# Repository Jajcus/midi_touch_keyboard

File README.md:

# MIDI Touch Keyboard

**Disclaimer**: this is a one-time personal hobby project. Shared as-is. Work
in progress. **Use at your own risk**, if at all.

This project is a device that lets you play MIDI synthesizer by touching
conducting surfaces, like fruits or vegetables.

It has 16 inputs (a bit over an octave), standard DIN-5 MIDI output and USB
MIDI interface. Additional controls include 'calibrate' button and a
'sensitivity' potentiometer.

A LED strip provides additional feedback displaying key state in piano-like layout.

## Working principle

Each 'input' is a simple capacitive sensor. Touching it either significantly
increases input capacitance or lowers its resistance to the device's ground. In
both cases this causes increase in the time constant of an RC circuit monitored
by a microcontroller.

The microcontroller charges the capacitance of the sensor circuit in short
intervals and checks if it discharges before a specific time. If it does, then
the input is open if it does not, it means the sensor has been touched.

The time to wait for discharging is determined through a calibration process
and the sensitivity potentiometer. The calibration process just measures the discharge times,
and collects maximum and minimum values measured, to roughly find the threshold
range. This assumes that at least one of the sensors has been touched during calibration.
Then the sensitivity knob can be used to set threshold within this range.

## Circuit design

The heart of the device is a Raspberry Pi Pico board. Cheap and powerful enough.

The sensor inputs are built using two resistors and a capacitor connected do
the microcontroller general-purpose IO pins. Values of those components has
been chosen experimentally to get quick and precise-enough measurements.

One pin is used to drive MIDI output. That is a standard circuit from the MIDI
1.0 specification using a transistor as the current loop switch (with a
Schottky diode for sharper edges).

Another pin drives addressable LED strip (WS2812B). Again, a transistor with a
Schottky diode is used to drive 5V data line here.

Two pins are used for button (actually only one used at the moment).

One ADC pin is connected to the sensitivity potentiometer. Another ADC pin is
connected to the sensors connector, so it can be used for detection of a device
connected there (in case I make one).

There is also an additional DC input, in case the micro-USB on the Pico is not
enough, because why not.

## Hardware realization

The device has been built on a single 'DIY' double-sided PCB, manufactured on a
small CNC engraver. Brass rivets are used for vias, otherwise no holes are
copper-plated. Most elements are surface mounted, 0603 size. The Raspberry Pi
Pico board is also surface-soldered to the main PCB, to keep overall low
profile (which the MIDI jack breaks anyway).

Sensor inputs are available via an angled 2x20 pin connector (like for an
old-style IDE HDD ribbon). Lower pins are all ground, sensors are on the upper
pins, starting from the third one. The last upper pin measures resistance to
the ground, for some auto-configuration capability in the future (not used now).

PCB layout is designed for my DIY constraints and the way I imagined the
complete device and is not suitable for most other fabrication processes.

The PCB design from KiCAD has been exported to Gerber files which would first
be converted to gcode by [pcb2gcode](https://github.com/pcb2gcode/pcb2gcode)
and then that gcode would be further processed by my
[postprocess.py](kicad/postprocess.py) script, for easier use with
[bCNC](https://github.com/vlachoudis/bCNC). Then couple of attempts and many
hours with the CNC machine and the PCB was ready for soldering. No soldermask,
unfortunately.

Even without the soldermask and with the small SMD components soldering was not
very hard. There was just a couple places that needed a do-over and proper
cleanup (the sensor circuit is quite sensitive to bad isolation, as 10 megaohm
resistors are used there).

The holes were drilled a bit to shallow, but that was not hard to fix, either.

## Firmware

The firmware is written in Rust, using the marvelous
[Embassy](https://embassy.dev/) framework. Nothing fancy otherwise.

One CPU core is dedicated for reading the sensors and UI inputs and basic
key-on/key-off logic. The other core does MIDI I/O over serial and USB.
Components communicate by passing messages via Embassy channels.

The LED strip programming uses Raspberry Pi Pico's PIO (programmable I/O), so
no bit-banging in CPU time is needed.

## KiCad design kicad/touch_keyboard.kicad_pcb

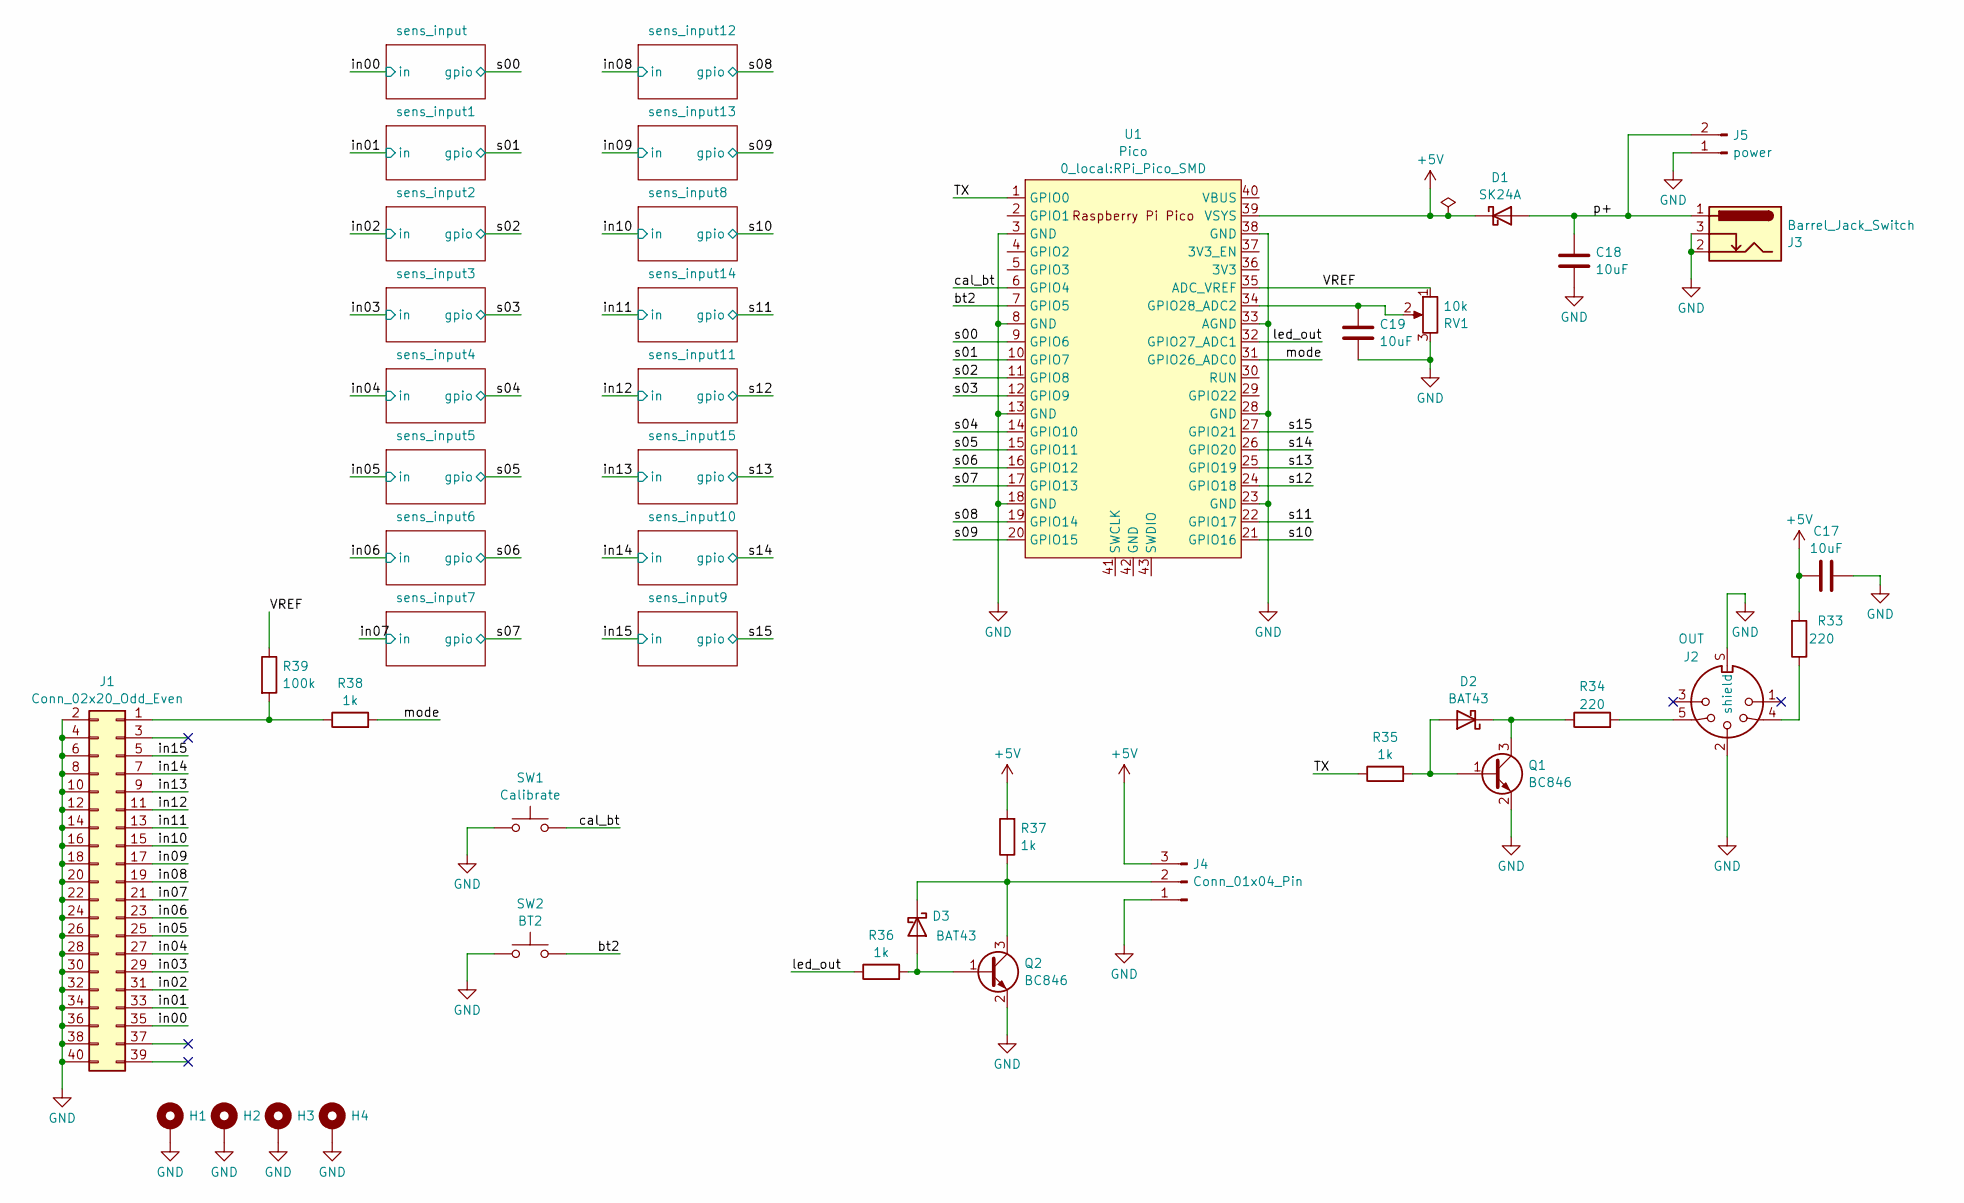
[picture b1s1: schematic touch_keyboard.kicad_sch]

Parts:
C17, C18, C19: 10uF; C_0805_2012Metric
D1: SK24A; D_SMA-SMB_Universal_Handsoldering
D2, D3: BAT43; D_MiniMELF
H1, H2, H3, H4: MountingHole_Pad; MountingHole_3.2mm_M3_DIN965_Pad
J1: Conn_02x20_Odd_Even; PinHeader_2x20_P2.54mm_Horizontal
J2: OUT; DIN_5
J3: Barrel_Jack_Switch; BarrelJack_CUI_PJ-063AH_Horizontal
J4: Conn_01x04_Pin; PinHeader_1x03_P2.54mm_Horizontal
J5: power; PinHeader_1x02_P2.54mm_Horizontal
Q1, Q2: BC846; SOT-23
R33, R34: 220; R_0603_1608Metric; MPN C22962
R35, R36, R37, R38: 1k; R_0603_1608Metric; MPN C22962
R39: 100k; R_0603_1608Metric; MPN C22962
RV1: 10k; Potentiometer_Bourns_PTV09A-1_Single_Vertical
SW1: Calibrate; Button
SW2: BT2; Button
U1: Pico; RPi_Pico_SMD

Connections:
+5V: C17.1, D1.1 (K), J4.3, R33.2, R37.2, U1.39 (VSYS)
/TX: R35.1, U1.1 (GPIO0)
/VREF: R39.1, RV1.1, U1.35 (ADC_VREF)
/bt2: SW2.2, U1.7 (GPIO5)
/cal_bt: SW1.2, U1.6 (GPIO4)
/in00: J1.35; also elsewhere on the board
/in01: J1.33; also elsewhere on the board
/in02: J1.31; also elsewhere on the board
/in03: J1.29; also elsewhere on the board
/in04: J1.27; also elsewhere on the board
/in05: J1.25; also elsewhere on the board
/in06: J1.23; also elsewhere on the board
/in07: J1.21; also elsewhere on the board
/in08: J1.19; also elsewhere on the board
/in09: J1.17; also elsewhere on the board
/in10: J1.15; also elsewhere on the board
/in11: J1.13; also elsewhere on the board
/in12: J1.11; also elsewhere on the board
/in13: J1.9; also elsewhere on the board
/in14: J1.7; also elsewhere on the board
/in15: J1.5; also elsewhere on the board
/led_out: R36.1, U1.32 (GPIO27_ADC1)
/mode: R38.2, U1.31 (GPIO26_ADC0)
/p+: C18.2, D1.2 (A), J3.1, J5.2
/s00: U1.9 (GPIO6); also elsewhere on the board
/s01: U1.10 (GPIO7); also elsewhere on the board
/s02: U1.11 (GPIO8); also elsewhere on the board
/s03: U1.12 (GPIO9); also elsewhere on the board
/s04: U1.14 (GPIO10); also elsewhere on the board
/s05: U1.15 (GPIO11); also elsewhere on the board
/s06: U1.16 (GPIO12); also elsewhere on the board
/s07: U1.17 (GPIO13); also elsewhere on the board
/s08: U1.19 (GPIO14); also elsewhere on the board
/s09: U1.20 (GPIO15); also elsewhere on the board
/s10: U1.21 (GPIO16); also elsewhere on the board
/s11: U1.22 (GPIO17); also elsewhere on the board
/s12: U1.24 (GPIO18); also elsewhere on the board
/s13: U1.25 (GPIO19); also elsewhere on the board
/s14: U1.26 (GPIO20); also elsewhere on the board
/s15: U1.27 (GPIO21); also elsewhere on the board
GND: C17.2, C18.1, C19.1, H1.1, H2.1, H3.1, H4.1, J1.2, J1.4, J1.6, J1.8, J1.10, J1.12, J1.14, J1.16, J1.18, J1.20, J1.22, J1.24, J1.26, J1.28, J1.30, J1.32, J1.34, J1.36, J1.38, J1.40, J2.2, J2.S (shield), J3.2, J3.3, J4.1, J5.1, Q1.2 (E), Q2.2 (E), RV1.3, SW1.1, SW2.1, U1.3 (GND), U1.8 (GND), U1.13 (GND), U1.18 (GND), U1.23 (GND), U1.28 (GND), U1.33 (AGND), U1.38 (GND); also elsewhere on the board
unnamed: D2.2 (A), Q1.1 (B), R35.2
unnamed: D2.1 (K), Q1.3 (C), R34.1
unnamed: D3.2 (A), Q2.1 (B), R36.2
unnamed: D3.1 (K), J4.2, Q2.3 (C), R37.1
unnamed: J1.1, R38.1, R39.2
unnamed: J2.4, R33.1
unnamed: J2.5, R34.2
unnamed: C19.2, RV1.2, U1.34 (GPIO28_ADC2)

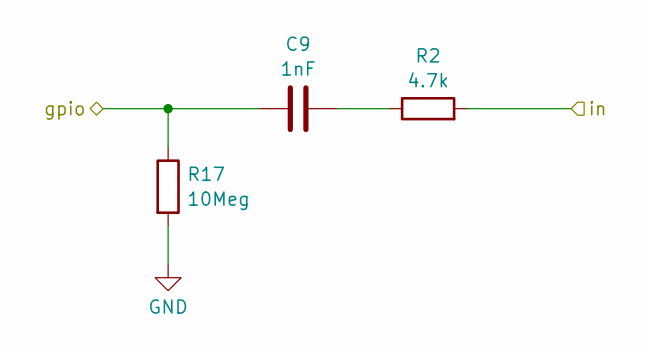
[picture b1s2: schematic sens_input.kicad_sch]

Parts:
C9: 1nF; C_0603_1608Metric
R2: 4.7k; R_0603_1608Metric
R17: 10Meg; R_0603_1608Metric

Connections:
/in00: R2.2; also elsewhere on the board
/s08: C9.1, R17.1; also elsewhere on the board
GND: R17.2; also elsewhere on the board

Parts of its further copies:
C1, C2, C3, C4, C5, C6, C7, C8, C10, C11, C12, C13, C14, C15, C16: 1nF; C_0603_1608Metric
R1, R3, R5, R7, R9, R11, R13, R15, R19, R21, R23, R25, R27, R29, R31: 10Meg; R_0603_1608Metric
R4, R6, R8, R10, R12, R14, R16, R18, R20, R22, R24, R26, R28, R30, R32: 4.7k; R_0603_1608Metric

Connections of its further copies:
/in01: R4.2; also elsewhere on the board
/in02: R6.2; also elsewhere on the board
/in03: R8.2; also elsewhere on the board
/in04: R10.2; also elsewhere on the board
/in05: R12.2; also elsewhere on the board
/in06: R14.2; also elsewhere on the board
/in07: R16.2; also elsewhere on the board
/in08: R18.2; also elsewhere on the board
/in09: R20.2; also elsewhere on the board
/in10: R22.2; also elsewhere on the board
/in11: R24.2; also elsewhere on the board
/in12: R26.2; also elsewhere on the board
/in13: R28.2; also elsewhere on the board
/in14: R30.2; also elsewhere on the board
/in15: R32.2; also elsewhere on the board
/s00: C1.1, R1.1; also elsewhere on the board
/s01: C2.1, R3.1; also elsewhere on the board
/s02: C3.1, R5.1; also elsewhere on the board
/s03: C4.1, R7.1; also elsewhere on the board
/s04: C5.1, R9.1; also elsewhere on the board
/s05: C6.1, R11.1; also elsewhere on the board
/s06: C7.1, R13.1; also elsewhere on the board
/s07: C8.1, R15.1; also elsewhere on the board
/s09: C10.1, R19.1; also elsewhere on the board
/s10: C11.1, R21.1; also elsewhere on the board
/s11: C12.1, R23.1; also elsewhere on the board
/s12: C13.1, R25.1; also elsewhere on the board
/s13: C14.1, R27.1; also elsewhere on the board
/s14: C15.1, R29.1; also elsewhere on the board
/s15: C16.1, R31.1; also elsewhere on the board
GND: R1.2, R3.2, R5.2, R7.2, R9.2, R11.2, R13.2, R15.2, R19.2, R21.2, R23.2, R25.2, R27.2, R29.2, R31.2; also elsewhere on the board
unnamed: C2.2, R4.1
unnamed: C3.2, R6.1
unnamed: C4.2, R8.1
unnamed: C5.2, R10.1
unnamed: C6.2, R12.1
unnamed: C7.2, R14.1
unnamed: C8.2, R16.1
unnamed: C10.2, R20.1
unnamed: C11.2, R22.1
unnamed: C12.2, R24.1
unnamed: C13.2, R26.1
unnamed: C14.2, R28.1
unnamed: C15.2, R30.1
unnamed: C16.2, R32.1

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
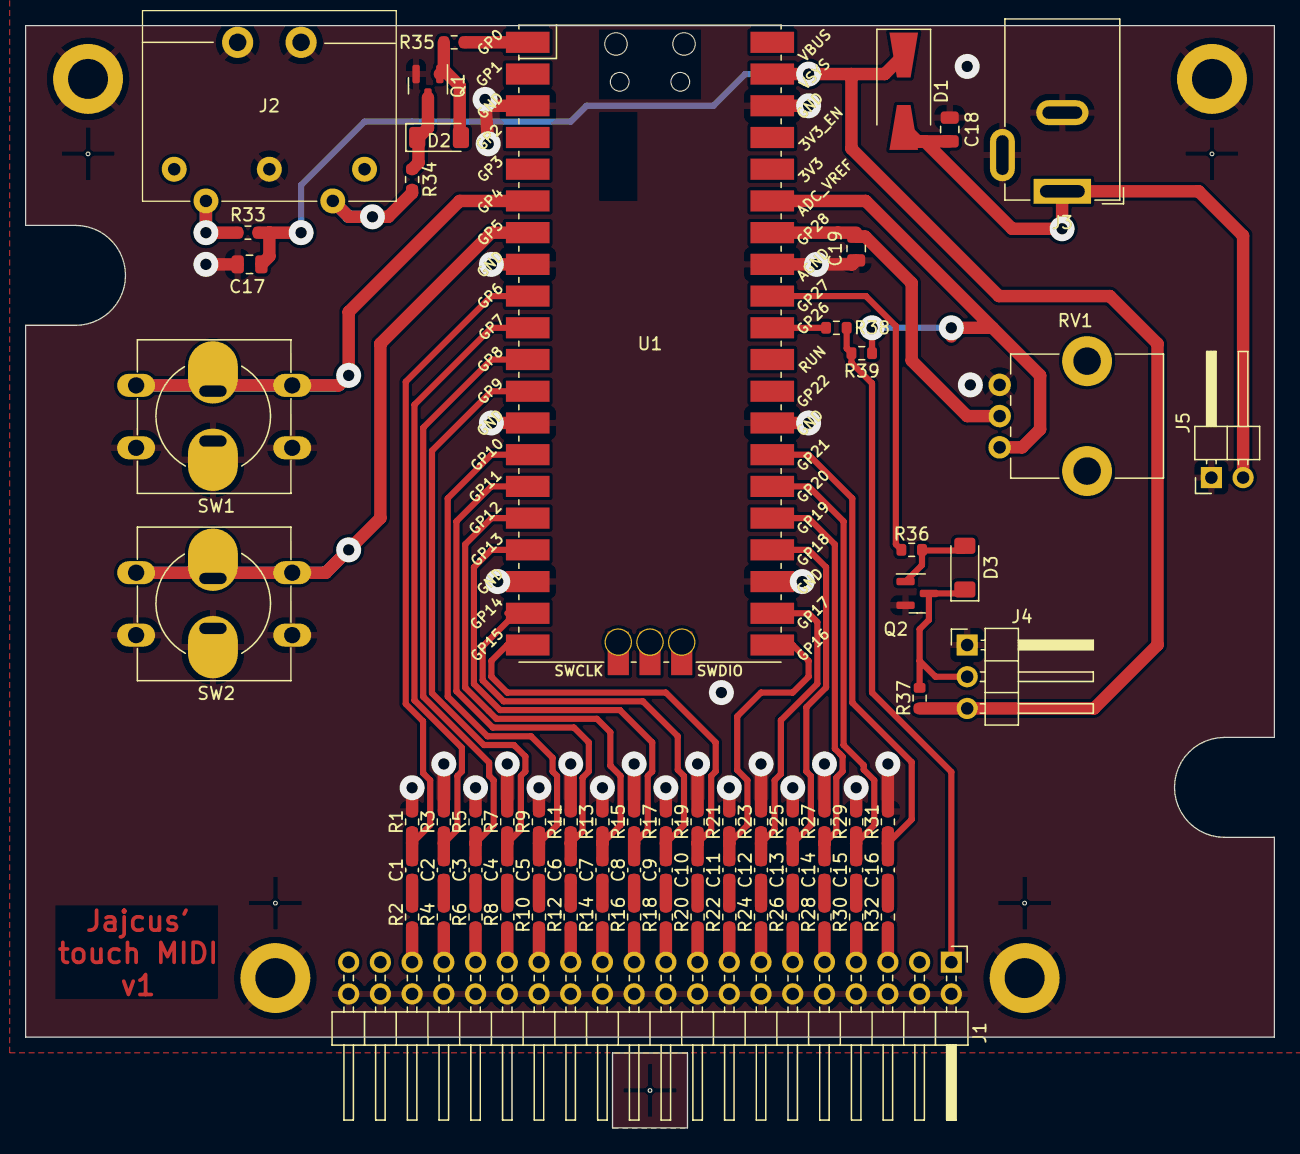
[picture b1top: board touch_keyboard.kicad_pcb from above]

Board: 2 copper layers, 100.0 x 88.3 mm, 76 parts (0 on the bottom side), 65 nets.

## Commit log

2024-02-02 initial import
    work in progress
2024-02-02 clippy fixes
2024-02-02 move configuration constants to a module
2024-02-02 sensing and LED improvements
2024-02-17 use 19 LEDs in piano keyboard layout
2024-02-27 circuit update
2024-02-27 adc code added
    will be used for sensitivity pot and 'mode' input pin
2024-03-07 code: add sensitivity control via pot
2024-03-15 map proper pin to the calibrate button
2024-03-19 code: serial MIDI output added
2024-03-20 update to the current version of the hardware
    includes pcb2gcode config and post-processing script
2024-03-20 move MIDI I/O to the second core
    only serial MIDI for now, but USB will be added later
2024-03-20 different colors for 'white' and 'black' keys
2024-03-24 usb_midi: collect multiple messages into the buffer
    for less latency / higher throughput… if anybody is able to play that fast ;)
2024-03-24 Default for AdcValues, by Clippy
2024-03-29 media files added
2024-03-29 README added
2024-03-29 preparing case design
2024-03-30 more media files
2024-03-30 README: fix addressable LED model name
2024-06-30 case added (as built)
